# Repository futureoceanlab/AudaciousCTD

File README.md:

# AudaciousCTD

To understand any phenomenon about the ocean, we need to understand its basic
physical properties. Conductivity, tempreature and pressure are  
common data to be collected to estimate the local salinity of seawater at
certain depths. They are measured by using a sensor referred to as a 
conductivity, temperature and depth (CTD) sensor. It turns out that the existing
technologies are extremely costly due to their precision and depth ratings 
(a list of quates from various companies are available in 
**Markeg_Survey.xlsx**). For some scientific studies, the precision and depth 
rating specifications from these manufacturers are important. However, 
their high cost prevent us from understanding beyond local phenomenon in 
the ocean. 

Ocean is dynamic from molecular to global physical scales. Therefore, it is not
sufficient to operate with a few great CTDs. If their cost of a CTD could be 
lowered, we could have a more detailed understanding of the ocean. Furthermore,
the entry barrier for people to help study the ocean would be lowered 
significantly. We hope to acheive that via Audacious CTD project.

## Software

This was the last version of the MCU code used for the first iteration of the
Audacious CTD. It has not been maintained since June 2019.

The MCU used in this iteration was a STM32F303. 

The role of the MCU is very simple. Every given period, it will sample
the conductivity, temperature and pressure data from its sensors. Then, it will
save them to the flash memory. 

To edit the code, we recommend the use of STM32 Cube IDE. To program
the MCU, we recommend the use of STM32CubeProgrammer. This software also
enables the user to directly import the data that have been written to the 
flash drive. We took this approach in the first iteration.

## Circuit
The latest version of the circuit has been added to this repository. There
are two separte parts. One part has an MCU and its peripherals, and another
part has sensor-related components. The MCU component was housed inside, and
the sensor component was potted in the endcap to expose the sensors to the
seawater. 

At the point of fabrication, we thought having two separate board layouts (one 
for inside the housing and another for exposed circuit with sensors) on one 
board would save cost. However, it only caused confusion on the manufacturing 
company, and we would highly advise simply making two separte boards.

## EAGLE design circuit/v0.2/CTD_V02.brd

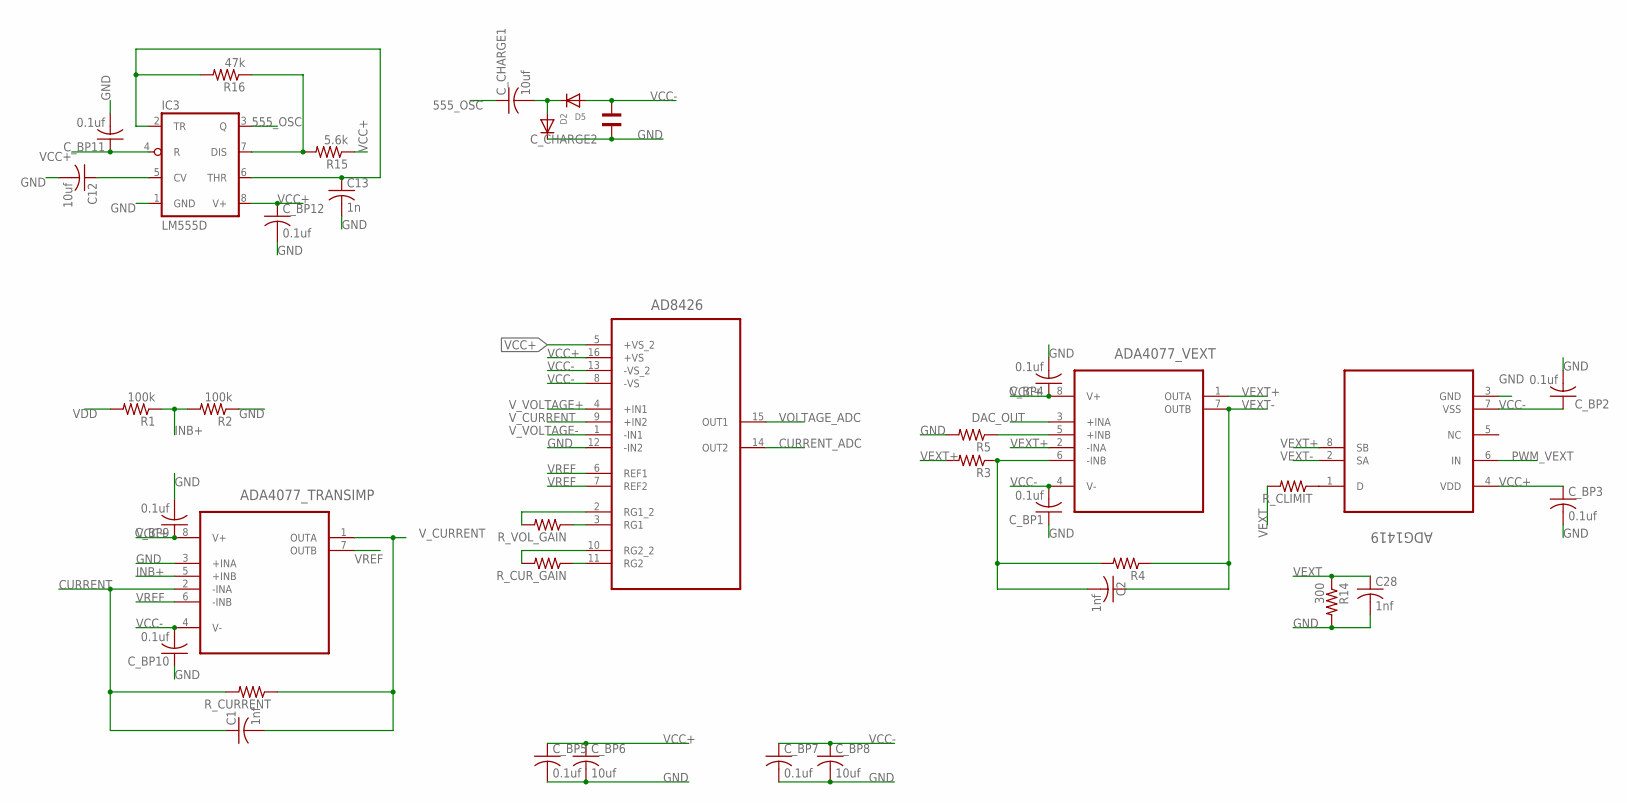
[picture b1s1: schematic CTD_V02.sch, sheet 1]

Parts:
AD8426: AD8426BCPZ-WP; QFN65P400X400X100-16N
ADA4077_TRANSIMP, ADA4077_VEXT: ADA4075-2ARZ; SOIC127P600X175-8N; MPN ADA4077
ADG1419: ADG1419BRMZ; SOP65P490X110-8N
C1, C2, C28: 1nf; C0603
C12: 10uf; C0603
C13: 1n; C0603
C_BP1, C_BP2, C_BP3, C_BP4, C_BP5, C_BP7, C_BP9, C_BP10, C_BP11, C_BP12: 0.1uf; C0603
C_BP6, C_BP8: 10uf; C0603
C_CHARGE1: 10uf; C0603
C_CHARGE2: WCAP-CSGP_1206_885012008001; WCAP-CSGP_1206
D2, D5: DIODESOD-123; SOD-123
IC3: LM555D; SO08
R1, R2: 100k; R0603
R3, R4, R5: R-US_R0603; R0603
R14: 300; R0603
R15: 5.6k; R0603
R16: 47k; R0603
R_CLIMIT: R-US_R0603; R0603
R_CURRENT: R-US_R0603; R0603
R_CUR_GAIN: R-US_R0603; R0603
R_VOL_GAIN: R-US_R0603; R0603

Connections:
555_OSC: C_CHARGE1.1, IC3.3 (Q)
CURRENT: ADA4077_TRANSIMP.2 (-INA), C1.1, R_CURRENT.2; also elsewhere on the board
CURRENT_ADC: AD8426.14 (OUT2); also elsewhere on the board
DAC_OUT: ADA4077_VEXT.3 (+INA); also elsewhere on the board
GND: AD8426.12 (-IN2), ADA4077_TRANSIMP.3 (+INA), ADG1419.3 (GND), C12.2, C13.2, C28.2, C_BP1.1, C_BP2.2, C_BP3.2, C_BP4.2, C_BP5.2, C_BP6.2, C_BP7.2, C_BP8.2, C_BP9.2, C_BP10.1, C_BP11.2, C_BP12.2, C_CHARGE2.2, D2.C, IC3.1 (GND), R2.1, R5.2, R14.2; also elsewhere on the board
INB+: ADA4077_TRANSIMP.5 (+INB), R1.1, R2.2
unnamed: AD8426.2 (RG1_2), R_VOL_GAIN.2
unnamed: AD8426.3 (RG1), R_VOL_GAIN.1
unnamed: AD8426.10 (RG2_2), R_CUR_GAIN.2
unnamed: ADA4077_VEXT.5 (+INB), R5.1
unnamed: AD8426.11 (RG2), R_CUR_GAIN.1
unnamed: ADA4077_VEXT.6 (-INB), C2.2, R3.1, R4.2
unnamed: IC3.7 (DIS), R15.2, R16.1
unnamed: C12.1, IC3.5 (CV)
unnamed: ADG1419.1 (D), R_CLIMIT.1
unnamed: C_CHARGE1.2, D2.A, D5.C
unnamed: C13.1, IC3.2 (TR), IC3.6 (THR), R16.2
PWM_VEXT: ADG1419.6 (IN); also elsewhere on the board
VCC+: AD8426.5 (+VS_2), AD8426.16 (+VS), ADA4077_TRANSIMP.8 (V+), ADA4077_VEXT.8 (V+), ADG1419.4 (VDD), C_BP3.1, C_BP4.1, C_BP5.1, C_BP6.1, C_BP9.1, C_BP11.1, C_BP12.1, IC3.4 (R), IC3.8 (V+), R15.1; also elsewhere on the board
VCC-: AD8426.8 (-VS), AD8426.13 (-VS_2), ADA4077_TRANSIMP.4 (V-), ADA4077_VEXT.4 (V-), ADG1419.7 (VSS), C_BP1.2, C_BP2.1, C_BP7.1, C_BP8.1, C_BP10.2, C_CHARGE2.1, D5.A
VDD: R1.2; also elsewhere on the board
VEXT: C28.1, R14.1, R_CLIMIT.2; also elsewhere on the board
VEXT+: ADA4077_VEXT.1 (OUTA), ADA4077_VEXT.2 (-INA), ADG1419.8 (SB), R3.2
VEXT-: ADA4077_VEXT.7 (OUTB), ADG1419.2 (SA), C2.1, R4.1
VOLTAGE_ADC: AD8426.15 (OUT1); also elsewhere on the board
VREF: AD8426.6 (REF1), AD8426.7 (REF2), ADA4077_TRANSIMP.6 (-INB), ADA4077_TRANSIMP.7 (OUTB)
V_CURRENT: AD8426.9 (+IN2), ADA4077_TRANSIMP.1 (OUTA), C1.2, R_CURRENT.1
V_VOLTAGE+: AD8426.4 (+IN1); also elsewhere on the board
V_VOLTAGE-: AD8426.1 (-IN1); also elsewhere on the board

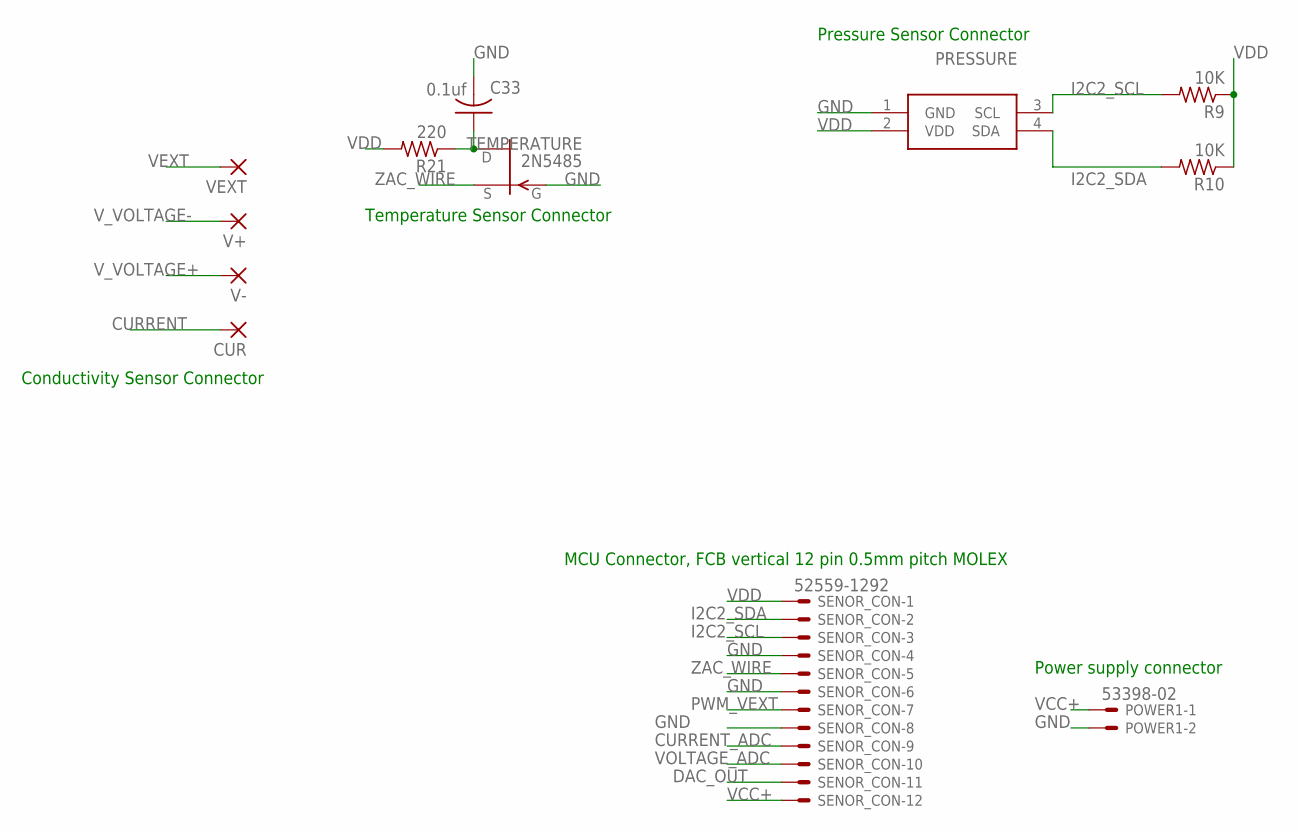
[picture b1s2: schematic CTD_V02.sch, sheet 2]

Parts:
C33: 0.1uf; C0603
CUR: SMD2; SMD1,27-2,54
POWER1: 53398-02
PRESSURE: MS583702BA01-50; MS583702BA0150
R9, R10: 10K; R0603
R21: 220; R0603
SENOR_CON: 52559-1292
TEMPERATURE: 2N5485; TO92-
V+: SMD2; SMD1,27-2,54
V-: SMD2; SMD1,27-2,54
VEXT: SMD2; SMD1,27-2,54

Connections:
CURRENT: CUR.1; also elsewhere on the board
CURRENT_ADC: SENOR_CON.9; also elsewhere on the board
DAC_OUT: SENOR_CON.11; also elsewhere on the board
GND: C33.2, POWER1.2, PRESSURE.1 (GND), SENOR_CON.4, SENOR_CON.6, SENOR_CON.8, TEMPERATURE.1 (G); also elsewhere on the board
I2C2_SCL: PRESSURE.3 (SCL), R9.2, SENOR_CON.3
I2C2_SDA: PRESSURE.4 (SDA), R10.2, SENOR_CON.2
unnamed: C33.1, R21.1, TEMPERATURE.3 (D)
PWM_VEXT: SENOR_CON.7; also elsewhere on the board
VCC+: POWER1.1, SENOR_CON.12; also elsewhere on the board
VDD: PRESSURE.2 (VDD), R9.1, R10.1, R21.2, SENOR_CON.1; also elsewhere on the board
VEXT: VEXT.1; also elsewhere on the board
VOLTAGE_ADC: SENOR_CON.10; also elsewhere on the board
V_VOLTAGE+: V-.1; also elsewhere on the board
V_VOLTAGE-: V+.1; also elsewhere on the board
ZAC_WIRE: SENOR_CON.5, TEMPERATURE.2 (S)

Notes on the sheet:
MCU Connector, FCB vertical 12 pin 0.5mm pitch MOLEX
Power supply connector
Conductivity Sensor Connector
Temperature Sensor Connector
Pressure Sensor Connector

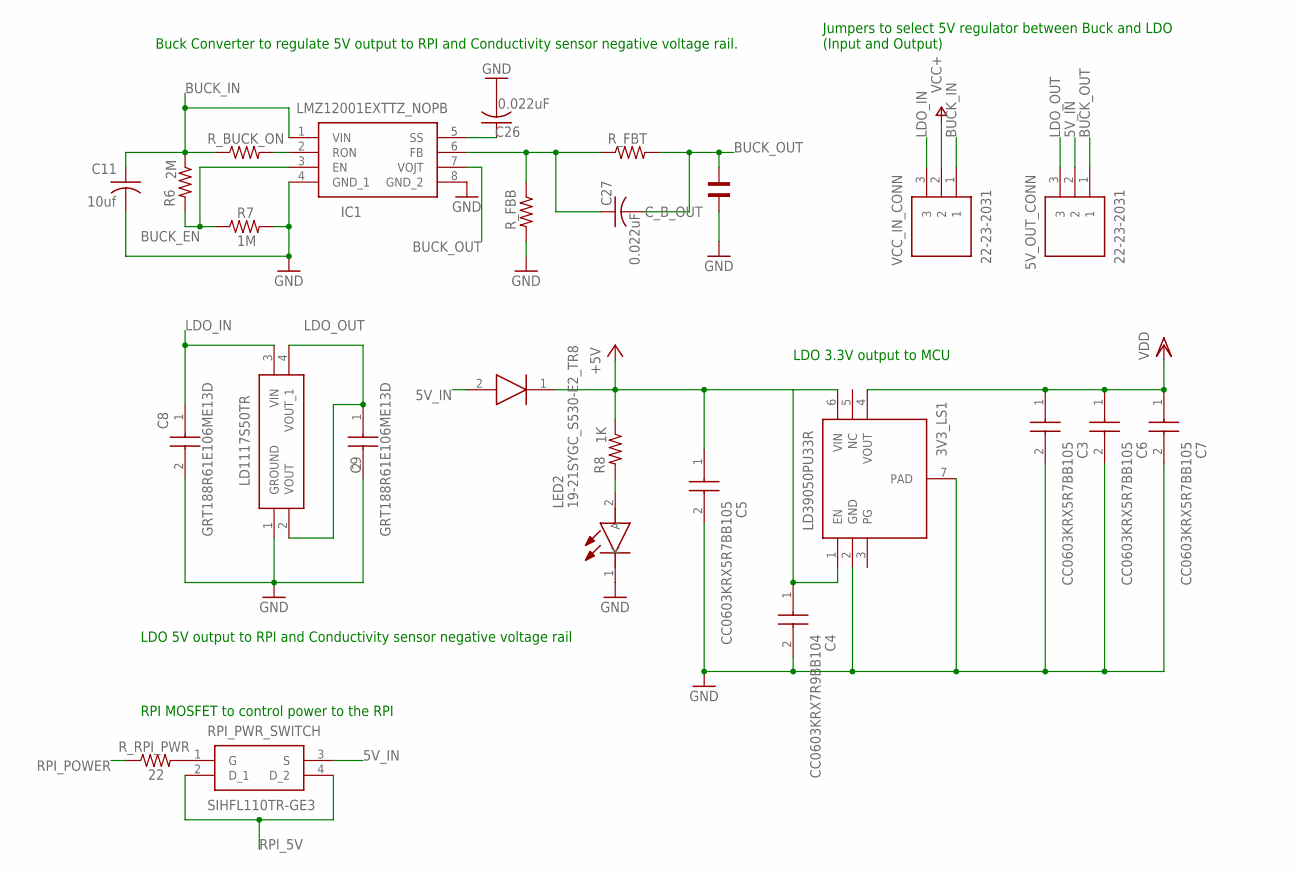
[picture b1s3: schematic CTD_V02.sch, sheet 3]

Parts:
3V3_LS1: LD39050PU33R; SON95P300X300X100-7N
5V_LS1: LD1117S50TR; SOT230P700X190-4N
5V_OUT_CONN: 22-23-2031; SHDR3W87P0X254_1X3_747X635X843
C3, C5, C6, C7: CC0603KRX5R7BB105; CAPC1608X90N
C4: CC0603KRX7R9BB104; CAPC1608X90N
C8, C9: GRT188R61E106ME13D; CAPC1608X100N
C11: 10uf; C0603
C26, C27: 0.022uF; C0603
C_B_OUT: WCAP-CSGP_1206_885012008001; WCAP-CSGP_1206
D3: STPS2L30A; DIOM5126X265N
IC1: LMZ12001EXTTZ_NOPB; NDW0007A
LED2: 19-21SYGC_S530-E2_TR8; LEDC1608X90N
R6: 2M; R0603
R7: 1M; R0603
R8: 1K; R0603
RPI_PWR_SWITCH: SIHFL110TR-GE3; SOT230P700X180-4N
R_BUCK_ON: R-US_R0603; R0603
R_FBB: R-US_R0603; R0603
R_FBT: R-US_R0603; R0603
R_RPI_PWR: 22; R0603
VCC_IN_CONN: 22-23-2031; SHDR3W87P0X254_1X3_747X635X843

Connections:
5V_IN: 5V_OUT_CONN.2, D3.2 (A), RPI_PWR_SWITCH.3 (S); also elsewhere on the board
+5V: 3V3_LS1.1 (EN), 3V3_LS1.6 (VIN), C4.1, C5.1, D3.1 (K), R8.1
BUCK_EN: IC1.3 (EN), R6.2, R7.1
BUCK_IN: C11.1, IC1.1 (VIN), R6.1, R_BUCK_ON.1, VCC_IN_CONN.1
BUCK_OUT: 5V_OUT_CONN.1, C27.2, C_B_OUT.1, IC1.7 (VOJT), R_FBT.2
GND: 3V3_LS1.2 (GND), 3V3_LS1.7 (PAD), 5V_LS1.1 (GROUND), C3.2, C4.2, C5.2, C6.2, C7.2, C8.2, C9.2, C11.2, C26.2, C_B_OUT.2, IC1.4 (GND_1), IC1.8 (GND_2), LED2.1 (K), R7.2, R_FBB.2; also elsewhere on the board
LDO_IN: 5V_LS1.3 (VIN), C8.1, VCC_IN_CONN.3
LDO_OUT: 5V_LS1.2 (VOUT), 5V_LS1.4 (VOUT_1), 5V_OUT_CONN.3, C9.1
unnamed: C27.1, IC1.6 (FB), R_FBB.1, R_FBT.1
unnamed: C26.1, IC1.5 (SS)
unnamed: IC1.2 (RON), R_BUCK_ON.2
unnamed: LED2.2 (A), R8.2
unnamed: RPI_PWR_SWITCH.1 (G), R_RPI_PWR.2
RPI_5V: RPI_PWR_SWITCH.2 (D_1), RPI_PWR_SWITCH.4 (D_2); also elsewhere on the board
RPI_POWER: R_RPI_PWR.1; also elsewhere on the board
VCC+: VCC_IN_CONN.2; also elsewhere on the board
VDD: 3V3_LS1.4 (VOUT), C3.1, C6.1, C7.1; also elsewhere on the board

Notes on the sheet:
Buck Converter to regulate 5V output to RPI and Conductivity sensor negative voltage rail.
LDO 5V output to RPI and Conductivity sensor negative voltage rail
LDO 3.3V output to MCU
Jumpers to select 5V regulator between Buck and LDO (Input and Output)
RPI MOSFET to control power to the RPI

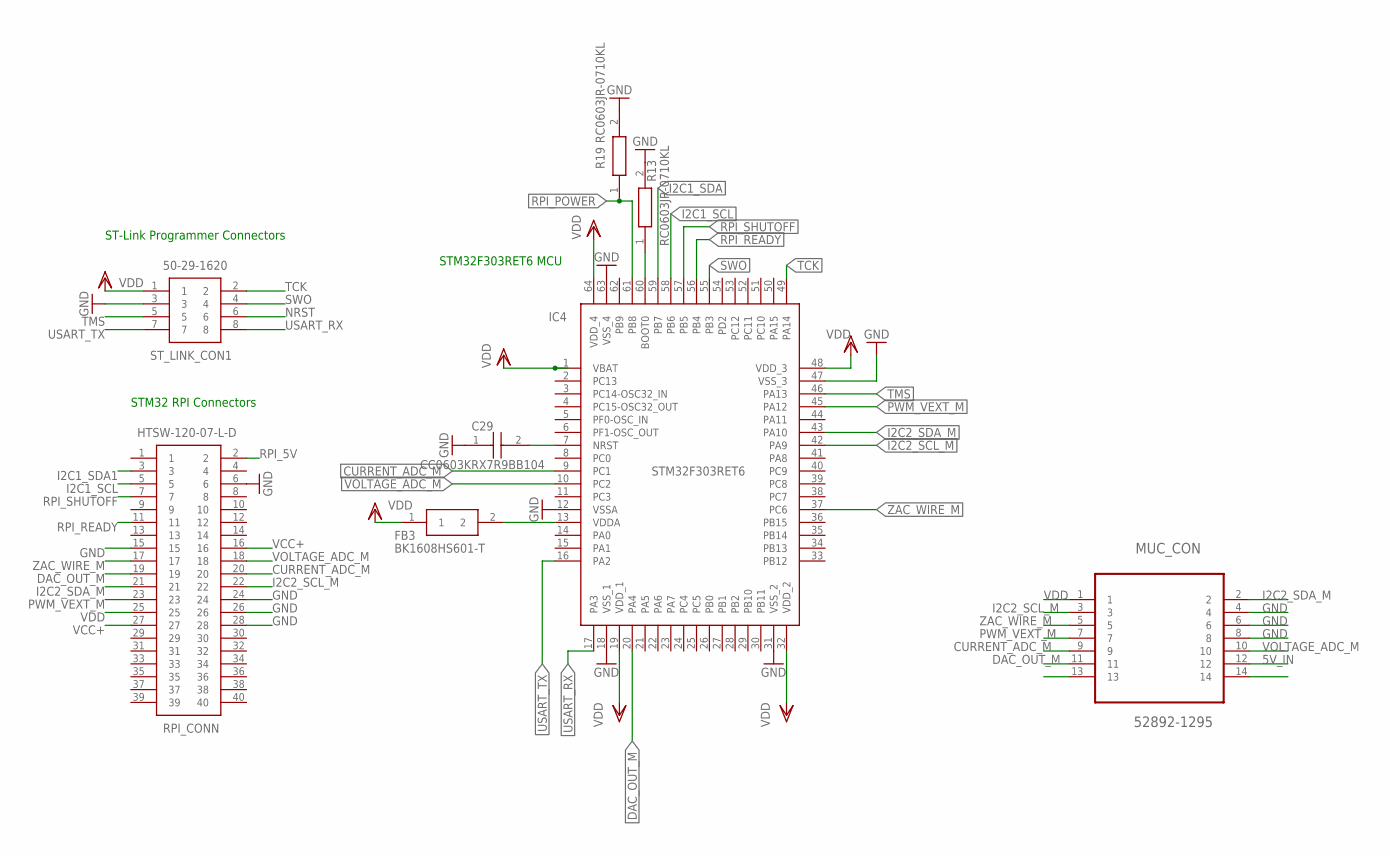
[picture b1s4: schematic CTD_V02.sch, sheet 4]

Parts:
C29: CC0603KRX7R9BB104; CAPC1608X90N
FB3: BK1608HS601-T; BEADC1608X95N
IC4: STM32F303RET6; QFP50P1200X1200X160-64N
MUC_CON: 52892-1295; MOLEX_52892-1295
R13, R19: RC0603JR-0710KL; RESC1608X55N
RPI_CONN: HTSW-120-07-L-D; SAMTEC_HTSW-120-07-L
ST_LINK_CON1: 50-29-1620; 50291620

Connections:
5V_IN: MUC_CON.12; also elsewhere on the board
CURRENT_ADC_M: IC4.9 (PC1), MUC_CON.9, RPI_CONN.20
DAC_OUT_M: IC4.20 (PA4), MUC_CON.11, RPI_CONN.19
GND: C29.1, IC4.12 (VSSA), IC4.18 (VSS_1), IC4.31 (VSS_2), IC4.47 (VSS_3), IC4.63 (VSS_4), MUC_CON.4, MUC_CON.6, MUC_CON.8, R13.2, R19.2, RPI_CONN.6, RPI_CONN.15, RPI_CONN.24, RPI_CONN.26, RPI_CONN.28, ST_LINK_CON1.3; also elsewhere on the board
I2C1_SCL: IC4.58 (PB6), RPI_CONN.5
I2C1_SDA: IC4.59 (PB7)
I2C1_SDA1: RPI_CONN.3
I2C2_SCL_M: IC4.42 (PA9), MUC_CON.3, RPI_CONN.22
I2C2_SDA_M: IC4.43 (PA10), MUC_CON.2, RPI_CONN.21
unnamed: IC4.60 (BOOT0), R13.1
unnamed: FB3.2, IC4.13 (VDDA)
NRST: C29.2, IC4.7 (NRST), ST_LINK_CON1.6
PWM_VEXT_M: IC4.45 (PA12), MUC_CON.7, RPI_CONN.23
RPI_5V: RPI_CONN.2; also elsewhere on the board
RPI_POWER: IC4.61 (PB8), R19.1; also elsewhere on the board
RPI_READY: IC4.56 (PB4), RPI_CONN.11
RPI_SHUTOFF: IC4.57 (PB5), RPI_CONN.7
SWO: IC4.55 (PB3), ST_LINK_CON1.4
TCK: IC4.49 (PA14), ST_LINK_CON1.2
TMS: IC4.46 (PA13), ST_LINK_CON1.5
USART_RX: IC4.17 (PA3), ST_LINK_CON1.8
USART_TX: IC4.16 (PA2), ST_LINK_CON1.7
VCC+: RPI_CONN.16, RPI_CONN.27; also elsewhere on the board
VDD: FB3.1, IC4.1 (VBAT), IC4.19 (VDD_1), IC4.32 (VDD_2), IC4.48 (VDD_3), IC4.64 (VDD_4), MUC_CON.1, RPI_CONN.25, ST_LINK_CON1.1; also elsewhere on the board
VOLTAGE_ADC_M: IC4.10 (PC2), MUC_CON.10, RPI_CONN.18
ZAC_WIRE_M: IC4.37 (PC6), MUC_CON.5, RPI_CONN.17

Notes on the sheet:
ST-Link Programmer Connectors
STM32F303RET6 MCU
STM32 RPI Connectors

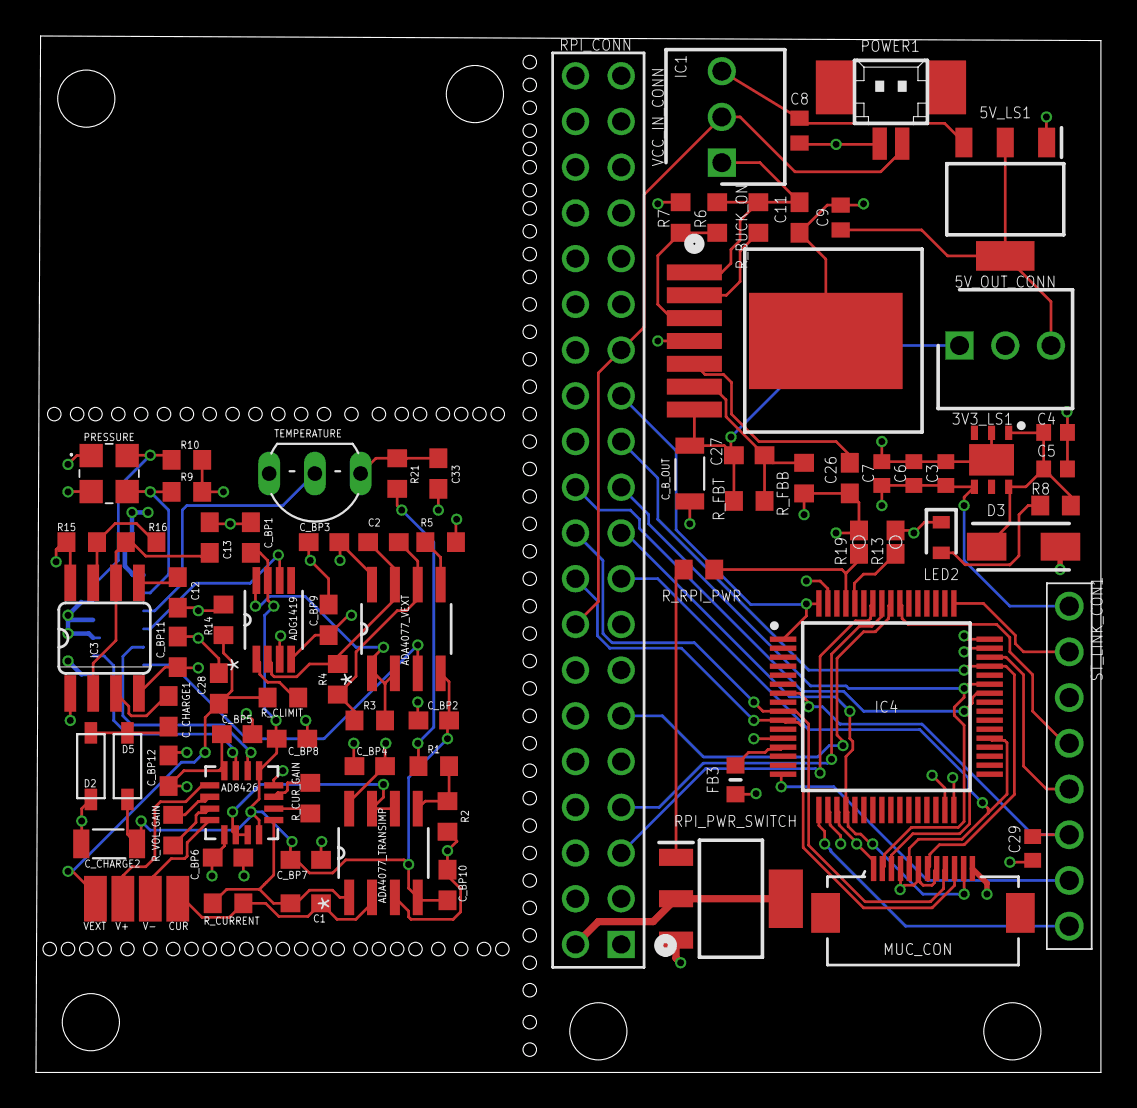
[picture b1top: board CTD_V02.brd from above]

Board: 4 copper layers, 59.2 x 57.6 mm, 84 parts (1 on the bottom side), 65 nets.

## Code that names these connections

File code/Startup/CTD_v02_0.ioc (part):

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Mcu.Name=STM32F303R(D-E)Tx
Mcu.Package=LQFP64
Mcu.UserName=STM32F303RETx
PA10.Mode=I2C
PA10.Signal=I2C2_SDA
PA12.GPIOParameters=GPIO_Label
PA12.GPIO_Label=PWM_Vext
PA12.Signal=GPIO_Output
PA13.GPIOParameters=GPIO_Label
PA13.GPIO_Label=TMS
PA13.Signal=SYS_JTMS-SWDIO
PA14.GPIOParameters=GPIO_Label
PA14.GPIO_Label=TCK
PA14.Signal=SYS_JTCK-SWCLK
PA2.GPIOParameters=GPIO_Label
PA2.GPIO_Label=USART_TX
PA2.Mode=Asynchronous
PA2.Signal=USART2_TX
PA3.GPIOParameters=GPIO_Label
PA3.GPIO_Label=USART_RX
PA3.Mode=Asynchronous
PA3.Signal=USART2_RX
PA4.Signal=COMP_DAC11_group
PA9.Mode=I2C
PA9.Signal=I2C2_SCL
PB3.GPIOParameters=GPIO_Label
PB3.GPIO_Label=SYS_STATUS
PB3.Signal=GPIO_Output
PB4.GPIOParameters=GPIO_Label
PB4.GPIO_Label=RPI_Ready
PB4.Signal=GPXTI4
PB5.GPIOParameters=GPIO_Label
PB5.GPIO_Label=RPI_Shutdown
PB5.Signal=GPIO_Output
PB6.Mode=I2C
PB6.Signal=I2C1_SCL
PB7.Mode=I2C
PB7.Signal=I2C1_SDA
PB8.GPIOParameters=GPIO_Label
PB8.GPIO_Label=RPI_Pwr_Enable
PB8.Signal=GPIO_Output
PC1.GPIOParameters=GPIO_Label
PC1.GPIO_Label=Current_ADC
PC1.Signal=ADCx_IN7
PC2.GPIOParameters=GPIO_Label
PC2.GPIO_Label=Voltage_ADC
PC2.Signal=ADCx_IN8
PC6.GPIOParameters=GPIO_Label
PC6.GPIO_Label=ZAC_Wire
PC6.Signal=S_TIM3_CH1
RCC.HSE_VALUE=8000000
RCC.SYSCLKFreq_VALUE=8000000
board=custom

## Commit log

2020-08-21 add the last version of the CTD MCU code
2020-08-21 add market survey
2020-08-21 initial explanation of the project
2020-08-21 explain about the programming
2020-08-25 add circuit schematic and layout
2020-08-25 add notes about the circuit

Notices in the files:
parts and their libraries:
Wurth_Elektronik_Passive_Capacitors_rev1: Copyright: Würth Elektronik
